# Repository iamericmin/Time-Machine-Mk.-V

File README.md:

# Time Machine Mk. V
# [Full write-up is on my website! It's also got links to my hackaday page, imgur album, and more goodies. You won't regret it](https://iamericmin.github.io/tm5.html)

## DIY nRF52 watch with BLE

Project status: idk

# hi
This is an update of my previous project, the Time Machine Mk. IV. It's better than its predecessor in almost every way I can imagine. There are still some minor bugs and kinks but I am super satisfied with how it turned out. It's got a cyberpunk themed design and motorsport-inspired livery.

# THE JUICY STUFF:
-   PROCESSOR: nRF52832 Soc. 64MHz ARM cortex M4 with 64k RAM and 512k flash.
-   FIRMWARE: Espruino JS interpreter + JS code. I'm working on a C/C++ version.
-   POWER: CR2032 coin cell battery. Guesstimated battery life of around a month.
-   DISPLAY: Dual 7-segment LEDs with five auxiliary LEDs.
-   INPUT: Triple momentary tactile switches.
-   SOUND: Mini piezo speaker.
-   DIMENSIONS: 43.18mm width and length, 9.2mm thickness(1mm thinner than the Mark IV!).
-   STRAP: 22mm NATO strap.

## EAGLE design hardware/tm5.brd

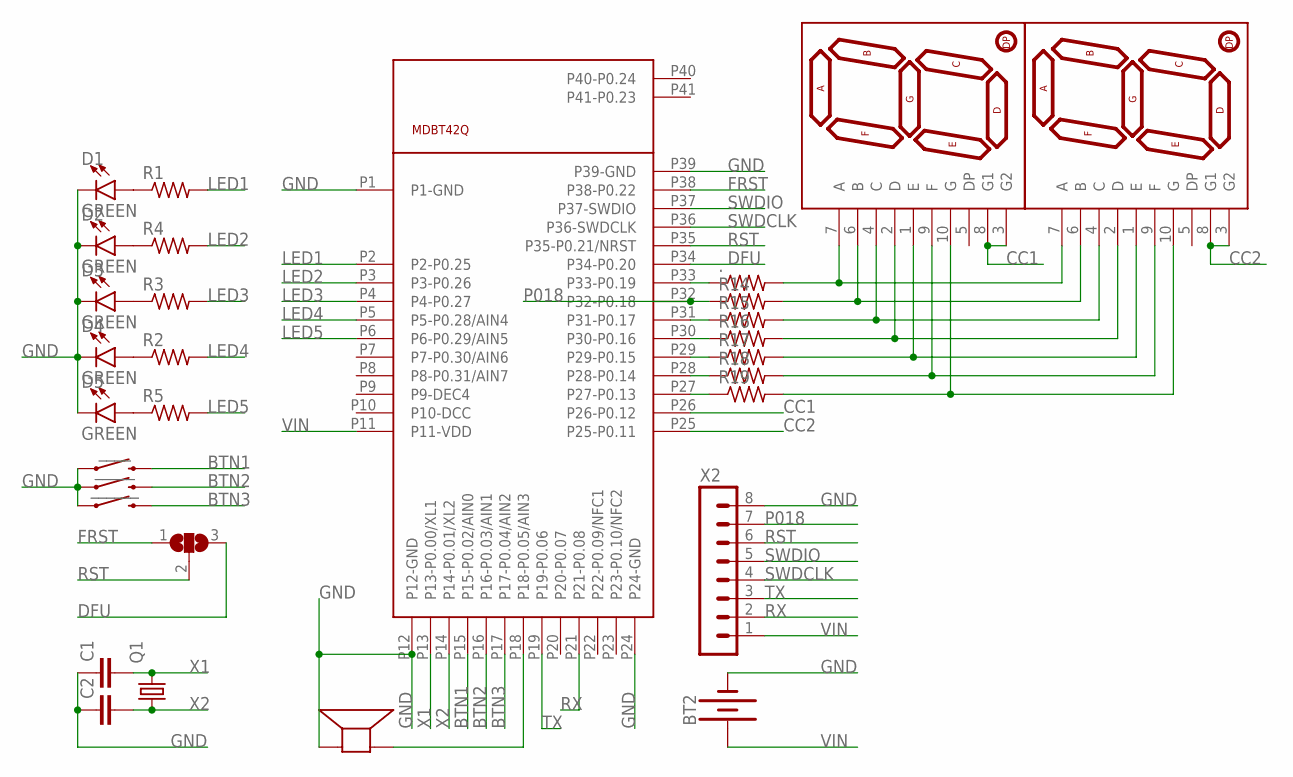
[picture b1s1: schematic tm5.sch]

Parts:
.: R-US_R0603; R0603
BT2: BATTERY-20MM_SMD_4LEGS_OVERPASTE; BATTCON_20MM_4LEGS_OVERPASTE
C1, C2: C-EUC0603; C0603
CFG: SJ2W; SJ_2
D1, D2, D3, D4, D5: GREEN; LED-1206
Q1: KX-327-NHT; 3.2X1.5
R1, R2, R3, R4, R5, R14, R15, R16, R17, R18, R19: R-US_R0603; R0603
SPK1: SMT-0540-S-R
U$1: MDBT42Q; MDBT40
U$2, U$3: 7-SEGMENT-DISPLAY-1"-RED; 7-SEGMENT-SMD
X2: SM08B-SRSS-TB
____: MOMENTARY-SWITCH-SPST-SMD-6.2MM-TALL; TACTILE_SWITCH_SMD_6.2MM_TALL
_____: MOMENTARY-SWITCH-SPST-SMD-6.2MM-TALL; TACTILE_SWITCH_SMD_6.2MM_TALL
______: MOMENTARY-SWITCH-SPST-SMD-6.2MM-TALL; TACTILE_SWITCH_SMD_6.2MM_TALL

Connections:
BTN1: U$1.P15 (P15-P0.02/AIN0), ____.B2 (2)
BTN2: U$1.P16 (P16-P0.03/AIN1), _____.B2 (2)
BTN3: U$1.P17 (P17-P0.04/AIN2), ______.B2 (2)
CC1: U$1.P26 (P26-P0.12), U$2.3 (G2), U$2.8 (G1)
CC2: U$1.P25 (P25-P0.11), U$3.3 (G2), U$3.8 (G1)
DFU: CFG.3, U$1.P34 (P34-P0.20)
FRST: CFG.1, U$1.P38 (P38-P0.22)
GND: BT2.2 (-), C1.1, C2.1, D1.C, D2.C, D3.C, D4.C, D5.C, SPK1.- (+), U$1.P1 (P1-GND), U$1.P12 (P12-GND), U$1.P24 (P24-GND), U$1.P39 (P39-GND), X2.8, ____.A2 (1), _____.A2 (1), ______.A2 (1)
LED1: R1.2, U$1.P2 (P2-P0.25)
LED2: R4.2, U$1.P3 (P3-P0.26)
LED3: R3.2, U$1.P4 (P4-P0.27)
LED4: R2.2, U$1.P5 (P5-P0.28/AIN4)
LED5: R5.2, U$1.P6 (P6-P0.29/AIN5)
unnamed: ..1, U$1.P33 (P33-P0.19)
unnamed: R15.1, U$1.P31 (P31-P0.17)
unnamed: D1.A, R1.1
unnamed: D2.A, R4.1
unnamed: D3.A, R3.1
unnamed: D4.A, R2.1
unnamed: R16.1, U$1.P30 (P30-P0.16)
unnamed: R17.1, U$1.P29 (P29-P0.15)
unnamed: R18.1, U$1.P28 (P28-P0.14)
unnamed: R19.1, U$1.P27 (P27-P0.13)
unnamed: ..2, U$2.7 (A), U$3.7 (A)
unnamed: SPK1.+ (-), U$1.P18 (P18-P0.05/AIN3)
unnamed: R14.2, U$2.6 (B), U$3.6 (B)
unnamed: R15.2, U$2.4 (C), U$3.4 (C)
unnamed: D5.A, R5.1
unnamed: R16.2, U$2.2 (D), U$3.2 (D)
unnamed: R17.2, U$2.1 (E), U$3.1 (E)
unnamed: R18.2, U$2.9 (F), U$3.9 (F)
unnamed: R19.2, U$2.10 (G), U$3.10 (G)
P018: R14.1, U$1.P32 (P32-P0.18), X2.7
RST: CFG.2, U$1.P35 (P35-P0.21/NRST), X2.6
RX: U$1.P21 (P21-P0.08), X2.2
SWDCLK: U$1.P36 (P36-SWDCLK), X2.4
SWDIO: U$1.P37 (P37-SWDIO), X2.5
TX: U$1.P19 (P19-P0.06), X2.3
VIN: BT2.1 (+), U$1.P11 (P11-VDD), X2.1
X1: C1.2, Q1.2, U$1.P13 (P13-P0.00/XL1)
X2: C2.2, Q1.1, U$1.P14 (P14-P0.01/XL2)

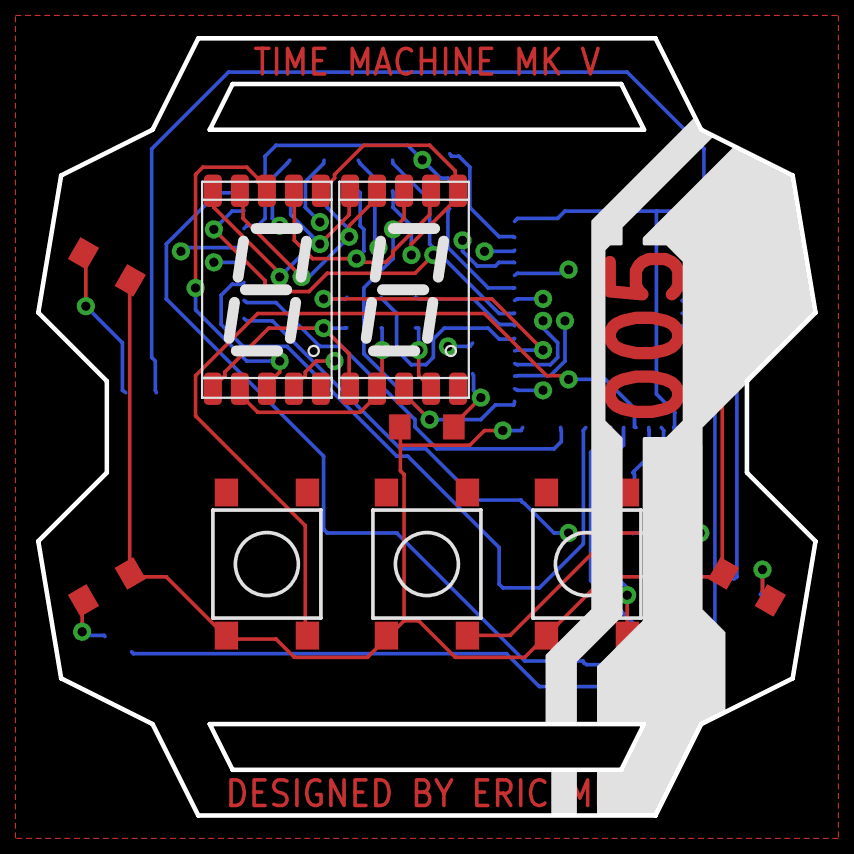
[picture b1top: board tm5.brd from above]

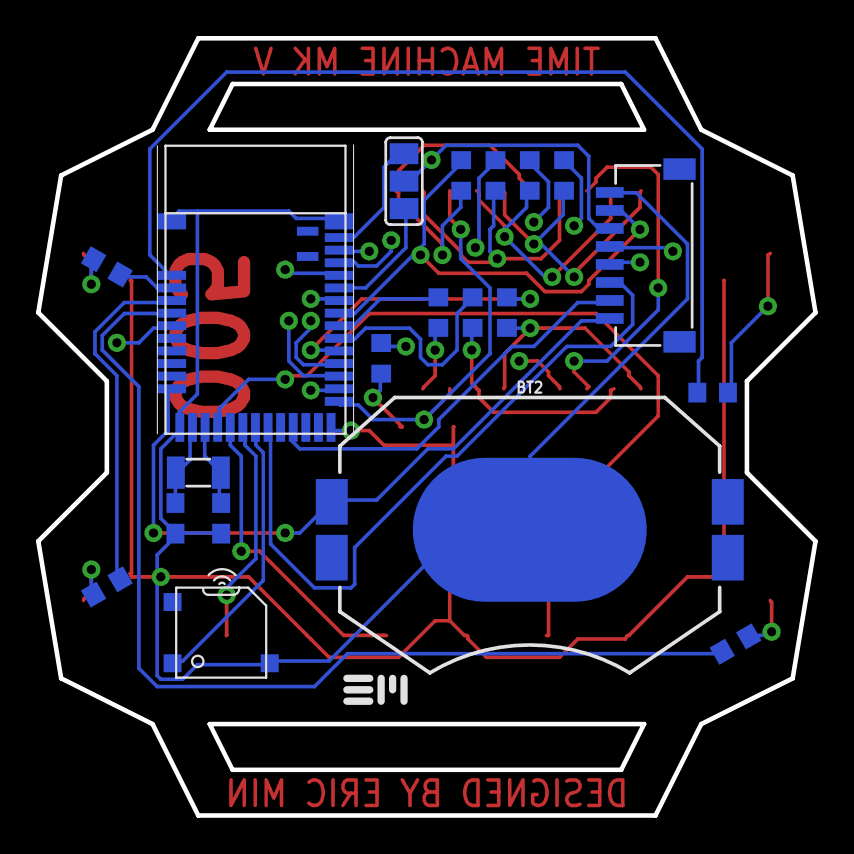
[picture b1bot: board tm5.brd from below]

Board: 4 copper layers, 43.2 x 43.2 mm, 30 parts (20 on the bottom side), 41 nets.

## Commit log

2020-08-11 first time be gentle
2021-02-14 shit

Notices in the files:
parts and their libraries:
SparkFun-Batteries: Licensing: Creative Commons ShareAlike 4.0 International - https://creativecommons.org/licenses/by-sa/4.0
crystal-geyer_V1_0: Copyright: Geyer-Electronic
